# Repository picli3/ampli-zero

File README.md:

# ampli-zero

Proyecto de amplificador de audio desarrollado en KiCad, orientado a una etapa de salida discreta y a la exploración práctica de una topología de amplificación analógica compacta.

## Propósito del proyecto
Este diseño parece estar pensado como una base para construir o experimentar con un amplificador de audio discreto, integrando los elementos necesarios de polarización, acoplo y etapa de potencia en una sola PCB.

## Qué incluye
- esquemático del amplificador
- diseño PCB en KiCad
- base reutilizable para análisis, pruebas y fabricación

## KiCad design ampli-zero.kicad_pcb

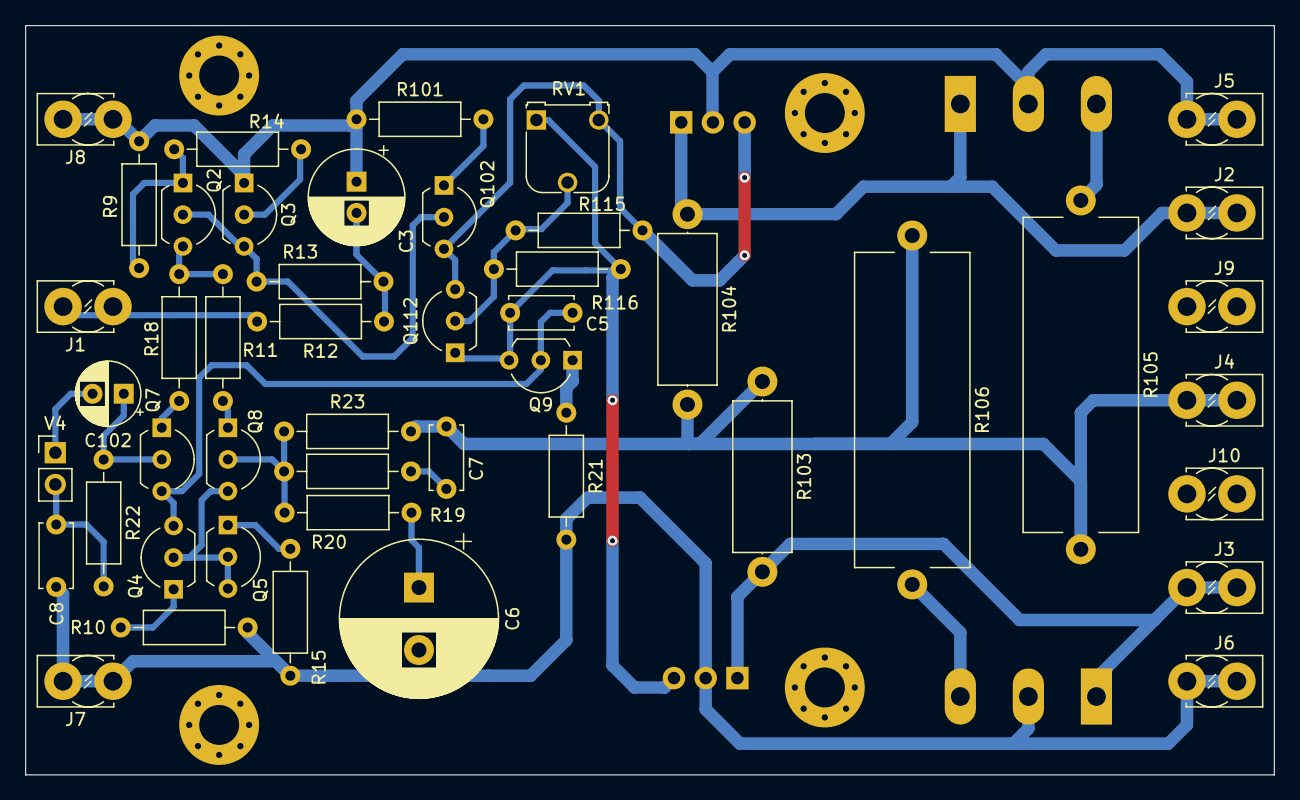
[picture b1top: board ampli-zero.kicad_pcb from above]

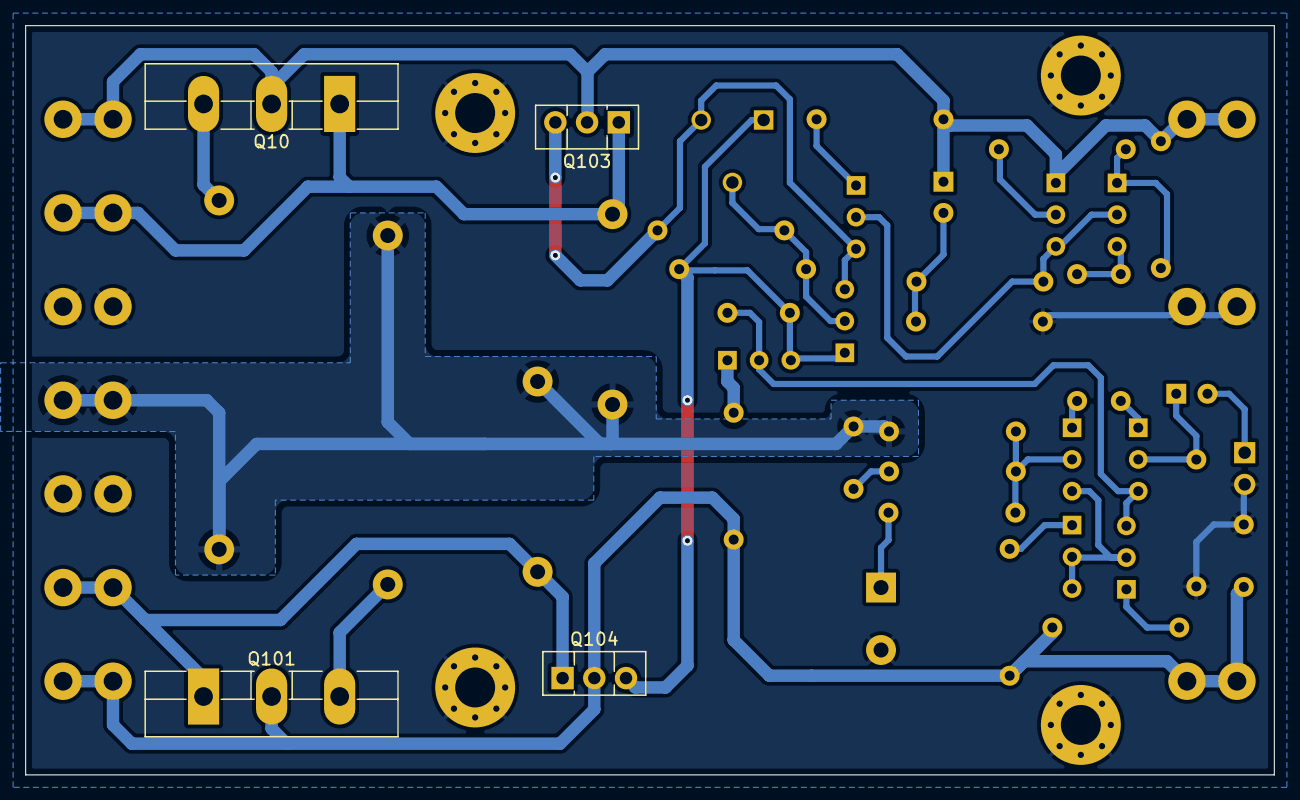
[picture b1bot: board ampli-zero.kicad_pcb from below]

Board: 2 copper layers, 100.0 x 60.0 mm, 55 parts (4 on the bottom side), 29 nets.

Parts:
C3: 10u; CP_Radial_D7.5mm_P2.50mm
C5: 150p; C_Disc_D5.0mm_W2.5mm_P5.00mm
C6: 220u; CP_Radial_D12.5mm_P5.00mm
C7: 100p; C_Disc_D5.0mm_W2.5mm_P5.00mm
C8: 100n; C_Disc_D5.0mm_W2.5mm_P5.00mm
C102: 3.3u; CP_Radial_D5.0mm_P2.50mm
H1, H2, H3, H4: MountingHole_Pad; MountingHole_3.2mm_M3_Pad_Via
J1, J2, J3, J4, J5, J6, J7, J8, J9, J10: Conn_01x01; TerminalBlock_MetzConnect_360322_1x01_Horizontal_ScrewM3.0_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
Q2, Q3, Q7, Q8, Q102: 2N5401; TO-92L_Inline_Wide
Q4, Q5, Q9, Q112: 2N5551; TO-92L_Inline_Wide
Q10: 2SC5200; TO-264-3_Vertical
Q101: 2SA1943; TO-264-3_Vertical
Q103: 2SD669; TO-126-3_Vertical
Q104: 2SB649; TO-126-3_Vertical
R9: 150; R_Axial_DIN0207_L6.3mm_D2.5mm_P10.16mm_Horizontal
R10, R15: 68; R_Axial_DIN0207_L6.3mm_D2.5mm_P10.16mm_Horizontal
R11, R18, R101: 100; R_Axial_DIN0207_L6.3mm_D2.5mm_P10.16mm_Horizontal
R12: 12k; R_Axial_DIN0207_L6.3mm_D2.5mm_P10.16mm_Horizontal
R13, R22: 10k; R_Axial_DIN0207_L6.3mm_D2.5mm_P10.16mm_Horizontal
R14, R20, R116: 1k; R_Axial_DIN0207_L6.3mm_D2.5mm_P10.16mm_Horizontal
R19: 220; R_Axial_DIN0207_L6.3mm_D2.5mm_P10.16mm_Horizontal
R21: 22; R_Axial_DIN0207_L6.3mm_D2.5mm_P10.16mm_Horizontal
R23: 91.13k; R_Axial_DIN0207_L6.3mm_D2.5mm_P10.16mm_Horizontal
R103, R104: 33; R_Axial_DIN0414_L11.9mm_D4.5mm_P15.24mm_Horizontal
R105, R106: 0.33; R_Axial_Power_L25.0mm_W9.0mm_P27.94mm
R115: 1; R_Axial_DIN0207_L6.3mm_D2.5mm_P10.16mm_Horizontal
RV1: 5k; Potentiometer_Runtron_RM-065_Vertical
V4: 1.76Vrms; PinHeader_1x02_P2.54mm_Vertical

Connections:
+107: C3.1, J5.1, J8.1, Q3.1 (E), Q10.2 (C), Q103.2 (C), R9.1, R101.1
-107: C8.1, J6.1, J7.1, Q101.2 (C), Q104.2 (C), R10.2, R15.2, R21.2
/FB: C7.2, J4.1, R23.2, R103.1, R104.2, R105.2, R106.1
/VB2: Q2.2 (B), Q3.3 (C), Q102.2 (B), R13.1
/VC2: Q2.3 (C), R11.1, R18.1
/VE2: Q2.1 (E), R9.2, R14.1
/gndv: C3.2, R12.1, R13.2
/v4i: C102.2, V4.1
/vdb: C5.2, Q9.3 (C), Q104.3 (B), Q112.1 (E), R116.2, RV1.1
/vdt: Q102.3 (C), Q103.3 (B), Q112.3 (C), R115.1, RV1.3
GND: C6.2, C8.2, H1.1, H2.1, H3.1, H4.1, J1.1, J9.1, J10.1, R12.2, R22.2, V4.2
unnamed: C6.1, R20.1
unnamed: C7.1, R19.2
unnamed: J2.1, Q10.1 (B), Q103.1 (E), R104.1
unnamed: J3.1, Q101.1 (B), Q104.1 (E), R103.2
unnamed: Q3.2 (B), R14.2
unnamed: Q4.2 (B), Q5.2 (B), Q5.3 (C), Q8.3 (C)
unnamed: C5.1, Q4.3 (C), Q7.3 (C), Q9.2 (B)
unnamed: Q4.1 (E), R10.1
unnamed: Q5.1 (E), R15.1
unnamed: C102.1, Q7.2 (B), R22.1
unnamed: Q7.1 (E), R18.2
unnamed: Q8.2 (B), R19.1, R20.2, R23.1
unnamed: Q8.1 (E), R11.2
unnamed: Q9.1 (E), R21.1
unnamed: Q10.3 (E), R105.1
unnamed: Q101.3 (E), R106.2
unnamed: Q102.1 (E), R101.2
unnamed: Q112.2 (B), R115.2, R116.1, RV1.2

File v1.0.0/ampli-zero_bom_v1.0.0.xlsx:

Item | References | Description | Qty | Package | Value | Aditional
1 | C7 | Unpolarized capacitor | 1 | C_Disc_D5.0mm_W2.5mm_P5.00mm | 100p | >100V
2 | C5 | Unpolarized capacitor | 1 | C_Disc_D5.0mm_W2.5mm_P5.00mm | 150p | >100V
3 | C8 | Unpolarized capacitor | 1 | C_Disc_D5.0mm_W2.5mm_P5.00mm | 100n | >100V
4 | C102 | Unpolarized capacitor | 1 | CP_Radial_D5.0mm_P2.50mm | 3.3u
5 | C3 | Polarized capacitor, US symbol | 1 | CP_Radial_D5.0mm_P2.50mm | 10u | >100V
6 | C6 | Polarized capacitor, US symbol | 1 | CP_Radial_D10.0mm_P5.00mm | 220u | >100V
7 | Q2 Q3 Q7 Q8 Q102 | PNP transistor, emitter/base/collector | 5 | TO-92L_Inline_Wide | 2N5401
8 | Q4 Q5 Q9 Q112 | NPN transistor, emitter/base/collector | 4 | TO-92L_Inline_Wide | 2N5551
9 | Q101 | PNP transistor, base/collector/emitter | 1 | TO-264-3_Vertical | 2SA1943
10 | Q104 | PNP transistor, emitter/collector/base | 1 | TO-126-3_Vertical | 2SB649
11 | Q10 | NPN transistor, base/collector/emitter | 1 | TO-264-3_Vertical | 2SC5200
12 | Q103 | NPN transistor, emitter/collector/base | 1 | TO-126-3_Vertical | 2SD669
13 | R105 R106 | Resistor, US symbol | 2 | R_Axial_Power_L25.0mm_W9.0mm_P27.94mm | 0.33 | 5W
14 | R21 | Resistor, US symbol | 1 | R_Axial_DIN0207_L6.3mm_D2.5mm_P10.16mm_Horizontal | 22 | 1/2W
15 | R103 R104 | Resistor, US symbol | 2 | R_Axial_DIN0414_L11.9mm_D4.5mm_P15.24mm_Horizontal | 33 | 1W
16 | R10 R15 | Resistor, US symbol | 2 | R_Axial_DIN0207_L6.3mm_D2.5mm_P10.16mm_Horizontal | 68 | 1/2W
17 | R11 R18 R101 | Resistor, US symbol | 3 | R_Axial_DIN0207_L6.3mm_D2.5mm_P10.16mm_Horizontal | 100 | 1/2W
18 | R9 | Resistor, US symbol | 1 | R_Axial_DIN0207_L6.3mm_D2.5mm_P10.16mm_Horizontal | 150 | 1/2W
19 | R19 | Resistor, US symbol | 1 | R_Axial_DIN0207_L6.3mm_D2.5mm_P10.16mm_Horizontal | 220 | 1/2W
20 | R116 | Resistor, US symbol | 1 | R_Axial_DIN0207_L6.3mm_D2.5mm_P10.16mm_Horizontal | 330 | 1/2W
21 | R14 R20 | Resistor, US symbol | 2 | R_Axial_DIN0207_L6.3mm_D2.5mm_P10.16mm_Horizontal | 1k | 1/2W
22 | R115 | Resistor, US symbol | 1 | R_Axial_DIN0207_L6.3mm_D2.5mm_P10.16mm_Horizontal | 1.2k | 1/2W
23 | R13 R22 | Resistor, US symbol | 2 | R_Axial_DIN0207_L6.3mm_D2.5mm_P10.16mm_Horizontal | 10k | 1/2W
24 | R12 | Resistor, US symbol | 1 | R_Axial_DIN0207_L6.3mm_D2.5mm_P10.16mm_Horizontal | 12k | 1/2W
25 | R23 | Resistor, US symbol | 1 | R_Axial_DIN0207_L6.3mm_D2.5mm_P10.16mm_Horizontal | 91.13k | 1/2W

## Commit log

2023-12-25 amplificador completado
2024-01-04 version de 32V
2024-01-06 version que enviada J Angel
2024-07-16 version desplegada sin probar
2024-07-16 agregando potenciometro
2024-07-16 enviado a pcbway
2026-04-29 Agrega README con descripción inicial del proyecto
2026-04-29 Mejora README con descripción específica del proyecto
